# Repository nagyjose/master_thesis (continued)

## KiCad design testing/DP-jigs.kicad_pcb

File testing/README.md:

# DP-jigs – Testovací a programovací přípravek (Bed-of-Nails)

> Specializovaný hardwarový testovací přípravek s pružinovými kontaktními hroty (pogo pins) určený pro rychlé oživování, nahrávání firmwaru a funkční diagnostiku jednotek **Kontrola** a **Závodník**.

**Stav projektu:** `Dokončeno / Funkční` | **Hlavní technologie:** `KiCad 9, Pogo Pins (Bed-of-Nails), IDC 2×22, SWD/JTAG, UART`

---

## 1. Účel a funkce

Při sériovější výrobě a osazování prototypů diplomové práce je nutné desky rychle a spolehlivě oživit, zkontrolovat napájecí větve a nahrát zaváděcí firmware bez nutnosti pájení dočasných drátových přívodů nebo osazování objemných konektorů na finální miniaturní desky.

Projekt `DP-jigs` řeší tuto úlohu pomocí koncepce **Bed-of-Nails** (jehličkového pole):
- **Odpružené zkušební hroty (Pogo pins):** 41 jednotlivých zlacených pružinových hrotů (pozice `J4` až `J45`) přesně lícujících s testovacími ploškami na spodní straně desek `DP-Kontrola` (PRJ-10) a `DP-Zavodnik` (PRJ-11).
- **Centrální rozhraní IDC (J1):** Dvouřadý konektor IDC 2×22 pinů s roztečí 2.54 mm slouží k propojení se stolními přístroji:
  - programátorem a debuggerem **ST-Link V2 / V3** (rozhraní SWD – SWDIO, SWCLK, NRST),
  - USB-UART převodníkem pro sledování výpisů ze sériové konzole mikrokontroléru a komunikaci s modemem Quectel BC660K,
  - laboratorním napájecím zdrojem (napájení primární větve VBAT nebo USB VBUS 5V),
  - měřicími body pro osciloskop, multimetr nebo logický analyzátor.

---

## 2. Architektura a princip fungování

```mermaid
flowchart LR
    subgraph Lab["Testovací a vývojové pracoviště"]
        STLink["ST-LINK V2/V3 (SWD rozhraní)"]
        USB_UART["USB-UART sériový převodník"]
        PSU["Laboratorní zdroj (3.3V / VBAT / 5V VBUS)"]
        DMM["Multimetr / Logický analyzátor"]
    end

    subgraph Jig["DP-jigs (Testovací přípravek)"]
        IDC["Centrální konektor J1 (IDC 2×22 pinů, RM 2.54 mm)"]
        PCB["2vrstvá deska plošných spojů (Nan-Ya NP-155FR)"]
        PogoField["Pole 41 pružinových hrotů (Pogo Pins J4–J45)"]

        IDC --> PCB --> PogoField
    end

    subgraph DUT["Testované moduly (Device Under Test)"]
        subgraph K["Jednotka Kontrola"]
            TP_K["Testovací plošky (SWD, UART, VDD, GND, NB-IoT)"]
        end
        subgraph Z["Jednotka Závodník"]
            TP_Z["Testovací plošky (SWD, VDD, VBAT, Senzory, GND)"]
        end
    end

    Lab --> IDC
    PogoField --> TP_K
    PogoField --> TP_Z
```

---

## 3. Hardware, schéma zapojení a PCB vizualizace

### Hlavní schéma a 3D model přípravku

*Obr. 1: Elektrické schéma zapojení propojující piny centrálního konektoru IDC 2×22 (J1) na 41 odpružených testovacích kontaktů.*

📄 [Otevřít schéma zapojení v plném rozlišení (PDF)](DP-jigs-schematic.pdf)

*Obr. 2: 3D pohled na sestavu testovacího přípravku s konektorem J1 a pogo kontakty.*

📄 [Otevřít montážní výkres layoutu v plném rozlišení (PDF)](DP-jigs-layout.pdf)

<details>
<summary>🔍 Zobrazit vrstvy layoutu PCB a montážní výkresy</summary>

#### Horní strana PCB (Top Copper – rozmístění pájecích bodů pogo pinů)

#### Spodní strana PCB (Bottom Copper – signálové cesty ke konektoru J1)

#### Vrtací plán plošných spojů (Drill Map)

#### Mechanický obrys přípravku a montážní otvory (Edge.Cuts)

</details>

---

## 4. Technické parametry desky přípravku

| Parametr | Specifikace |
| :--- | :--- |
| **Typ desky** | 2vrstvá DPS (Nan-Ya NP-155FR core, JLCPCB stackup) |
| **Tloušťka DPS** | 1.6062 mm (zvýšená tuhost proti prohnutí při stlačení hrotů) |
| **Povrchová úprava** | HASL / ENIG pro spolehlivý kontakt pájecích plošek |
| **Konektor rozhraní** | 1× IDC Header 2×22 pinů vertikální, rozteč 2.54 mm (`J1`) |
| **Kontaktní hroty** | 41× zlacený pogo pin v pouzdře vertikálního kolíku (`J4`–`J45`) |
| **Fixace DUT desek** | Mechanické naváděcí kolíky pro přesné usazení desek z DP-Panelu |

---

## 5. Struktura adresáře

```text
.
├── DP-jigs.kicad_pcb                 # Návrh 2vrstvé desky testovacího přípravku v KiCad 9
├── DP-jigs.kicad_pro                 # Projektová konfigurace KiCad
├── DP-jigs.kicad_sch                 # Elektrické schéma zapojení (propojení J1 na pogo piny)
├── DP-jigs-schematic.pdf             # Vektorové schéma v PDF v plném rozlišení
├── DP-jigs-layout.pdf                # Celkový osazovací a montážní výkres přípravku
├── DP-jigs-layout-part-1..4.pdf      # Detailní výkresy jednotlivých sekcí a kvadrantů
├── DP-jigs-view-1.png                # 3D fotorealistický render desky přípravku
├── docs/images/                      # Optimalizované PNG náhledy pro dokumentaci
├── fabrication-toolkit-options.json  # Exportní nastavení pro KiCad Fabrication Toolkit
├── production/ (fab-data/)           # Výrobní podklady pro JLCPCB
│   ├── DP-jigs.zip                   # Archiv s Gerber vrstvami a Excellon vrty
│   ├── bom.csv                       # Kusovník součástek (J1 IDC lišta + pogo piny)
│   ├── positions.csv                 # Souřadnice pro strojní osazení konektoru a pinů
│   ├── designators.csv               # Seznam referenčních značek
│   └── netlist.ipc                   # IPC-D-356 kontrolní netlist
└── README.md                         # Tato dokumentace
```

---

## 6. Mapování signálů a konektoru J1

Schéma `DP-jigs.kicad_sch` definuje přímé vedení z pinů dvouřadého konektoru `J1` na jednotlivé odpružené hroty. Rozložení je rozděleno do funkčních bloků:

1. **Napájení a zem (Power & GND):**
   - Vícenásobné piny GND pro zajištění nízké impedance a spolehlivého návratového proudu.
   - Piny pro externí napájení větví 3.3 V (`VDD_MCU`), `VBAT` (simulace Li-Ion akumulátoru) a `VBUS_5V` (simulace USB napájení).
2. **Programovací rozhraní SWD (Serial Wire Debug):**
   - Vyvedeno pro kontrolér STM32WB55 jednotky Kontrola i Závodník (`SWDIO`, `SWCLK`, `NRST`, volitelně `SWO`).
3. **Komunikační sběrnice:**
   - UART TX/RX linky pro ladicí logy firmwaru.
   - Komunikační linky modemu BC660K pro přímou diagnostiku AT příkazů.
4. **Měřicí a stavové signály:**
   - Přístup k výstupům napěťových monitorů baterie a signálům bezdrátového Qi přijímače.

---

## 7. Doporučený postup oživování (Bring-up Workflow)

1. **Vizuální kontrola:** Před usazením testované desky do přípravku zkontrolujte, zda žádný z pogo hrotů není ohnutý nebo mechanicky zablokovaný.
2. **Připojení laboratorního zdroje:** Zdroj nastavte na 3.7 V (VBAT) nebo 5.0 V (VBUS) s proudovým omezením na max. 100 mA pro detekci případného zkratu na desce.
3. **Usazení testované desky:** Desku (oddělenou z `DP-Panel`) přiložte na naváděcí kolíky přípravku a rovnoměrným tlakem zajistěte kontakt všech testovacích bodů.
4. **Ověření napětí:** Multimetrem zkontrolujte výstupy regulátorů TPS62842 (3.3 V) a funkčnost PMIC obvodů.
5. **Flashování firmwaru:** Připojte ST-Link V2/V3 a nahrajte inicializační bootloader a aplikační kód ze složek `Kontrola_Syst` resp. `Zavodnik_Syst`.
6. **Funkční test:** Pomocí terminálu UART ověřte úspěšný start systému a vysílání rádiového majáku.

---

## 8. Návaznost na ostatní projekty

Projekt `DP-jigs` je v rámci repozitáře **DP** (`nagyjose/DP` / `nagyjose/master_thesis`) začleněn do složky testovacích prostředků `testing/`:
- **PRJ-10 (DP-Kontrola):** Primární testovaná jednotka základny.
- **PRJ-11 (DP-Zavodnik):** Primární testovaná jednotka závodníka.
- **PRJ-12 (DP-Panel):** Výrobní sestava, ze které desky pocházejí.
- **Kontrola_Syst / Zavodnik_Syst:** Firmwary v jazyce C vyvíjené a laděné pomocí tohoto přípravku.

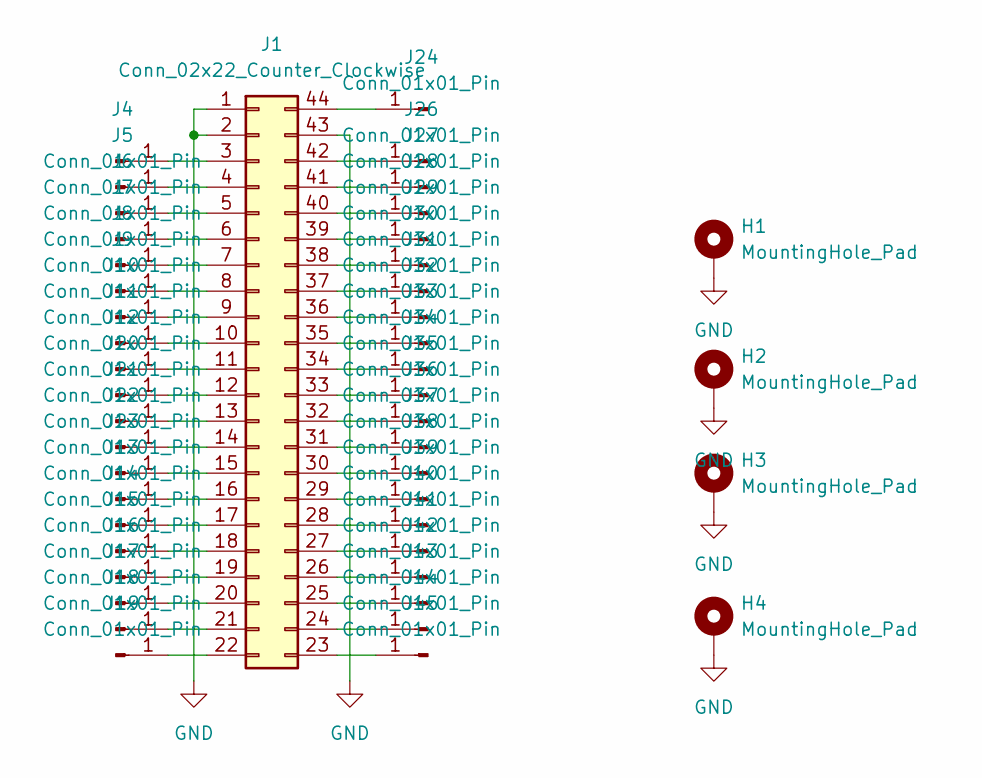
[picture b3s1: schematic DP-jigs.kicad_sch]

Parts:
H1, H2, H3, H4: MountingHole_Pad; MountingHole_3.2mm_M3_Pad_Via
J1: Conn_02x22_Counter_Clockwise; IDC-Header_2x22_P2.54mm_Vertical
J4, J5, J6, J7, J8, J9, J10, J11, J12, J13, J14, J15, J16, J17, J18, J19, J20, J21, J22, J23, J24, J26, J27, J28, J29, J30, J31, J32, J33, J34, J35, J36, J37, J38, J39, J40, J41, J42, J43, J44, J45: Conn_01x01_Pin; PinHeader_1x01_P2.54mm_Vertical

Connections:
GND: H1.1, H2.1, H3.1, H4.1, J1.1, J1.2, J1.43; also elsewhere on the board
unnamed: J1.3, J4.1
unnamed: J1.4, J5.1
unnamed: J1.5, J6.1
unnamed: J1.6, J7.1
unnamed: J1.7, J8.1
unnamed: J1.8, J9.1
unnamed: J1.9, J10.1
unnamed: J1.10, J11.1
unnamed: J1.11, J12.1
unnamed: J1.12, J20.1
unnamed: J1.13, J21.1
unnamed: J1.14, J22.1
unnamed: J1.15, J23.1
unnamed: J1.16, J13.1
unnamed: J1.17, J14.1
unnamed: J1.18, J15.1
unnamed: J1.19, J16.1
unnamed: J1.20, J17.1
unnamed: J1.21, J18.1
unnamed: J1.22, J19.1
unnamed: J1.23, J45.1
unnamed: J1.24, J44.1
unnamed: J1.25, J43.1
unnamed: J1.26, J42.1
unnamed: J1.27, J41.1
unnamed: J1.28, J40.1
unnamed: J1.29, J39.1
unnamed: J1.30, J38.1
unnamed: J1.31, J37.1
unnamed: J1.32, J36.1
unnamed: J1.33, J35.1
unnamed: J1.34, J34.1
unnamed: J1.35, J33.1
unnamed: J1.36, J32.1
unnamed: J1.37, J31.1
unnamed: J1.38, J30.1
unnamed: J1.39, J29.1
unnamed: J1.40, J28.1
unnamed: J1.41, J27.1
unnamed: J1.42, J26.1
unnamed: J1.44, J24.1

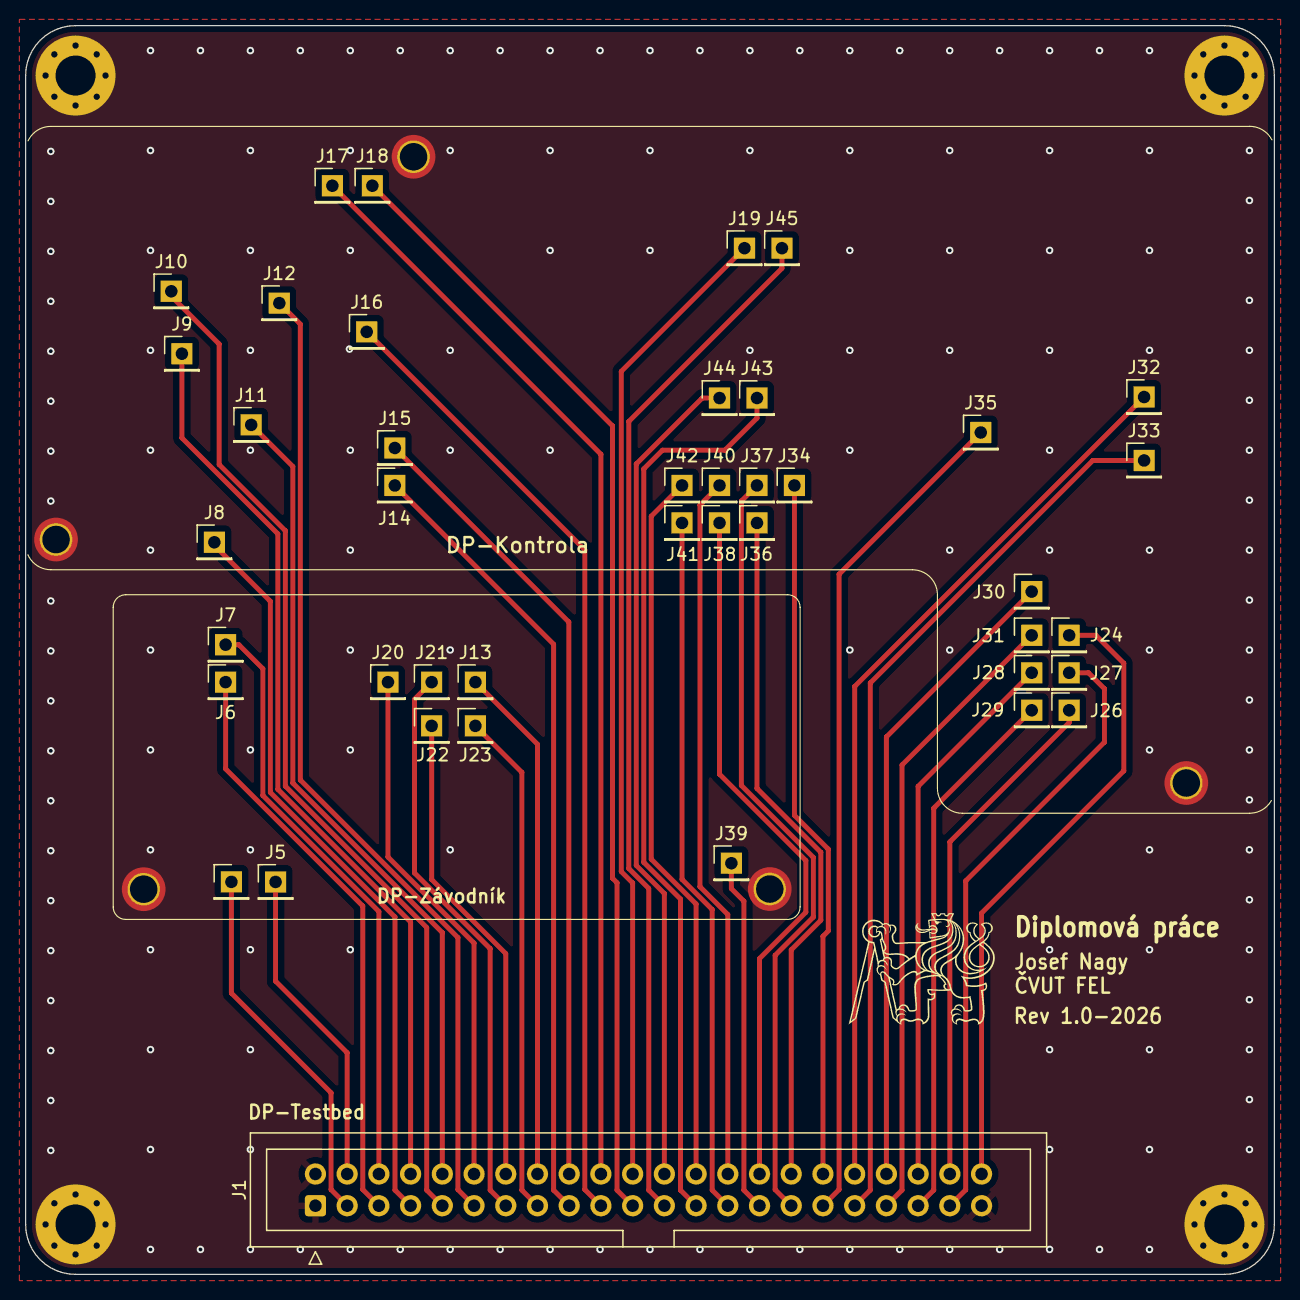
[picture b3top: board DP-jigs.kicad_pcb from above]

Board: 2 copper layers, 100.0 x 100.0 mm, 51 parts (0 on the bottom side), 42 nets.

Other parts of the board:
H1#2, H81, H82: MountingHole_Pad; MountingHole_2.2mm_M2_ISO7380_Pad_TopBottom
H2#2, H3#2: MountingHole_Pad; MountingHole_3.2mm_M3_Pad_Via

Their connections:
GND: H1#2.1, H2#2.1, H3#2.1, H81.1, H82.1; also elsewhere on the board

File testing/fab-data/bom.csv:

Designator,Footprint,Quantity,Value,LCSC Part #
J1,IDC-Header_2x22_P2.54mm_Vertical,1,Conn_02x22_Counter_Clockwise,
"J10, J11, J12, J13, J14, J15, J16, J17, J18, J19, J20, J21, J22, J23, J24, J26, J27, J28, J29, J30, J31, J32, J33, J34, J35, J36, J37, J38, J39, J4, J40, J41, J42, J43, J44, J45, J5, J6, J7, J8, J9",PinHeader_1x01_P2.54mm_Vertical,41,Conn_01x01_Pin,
